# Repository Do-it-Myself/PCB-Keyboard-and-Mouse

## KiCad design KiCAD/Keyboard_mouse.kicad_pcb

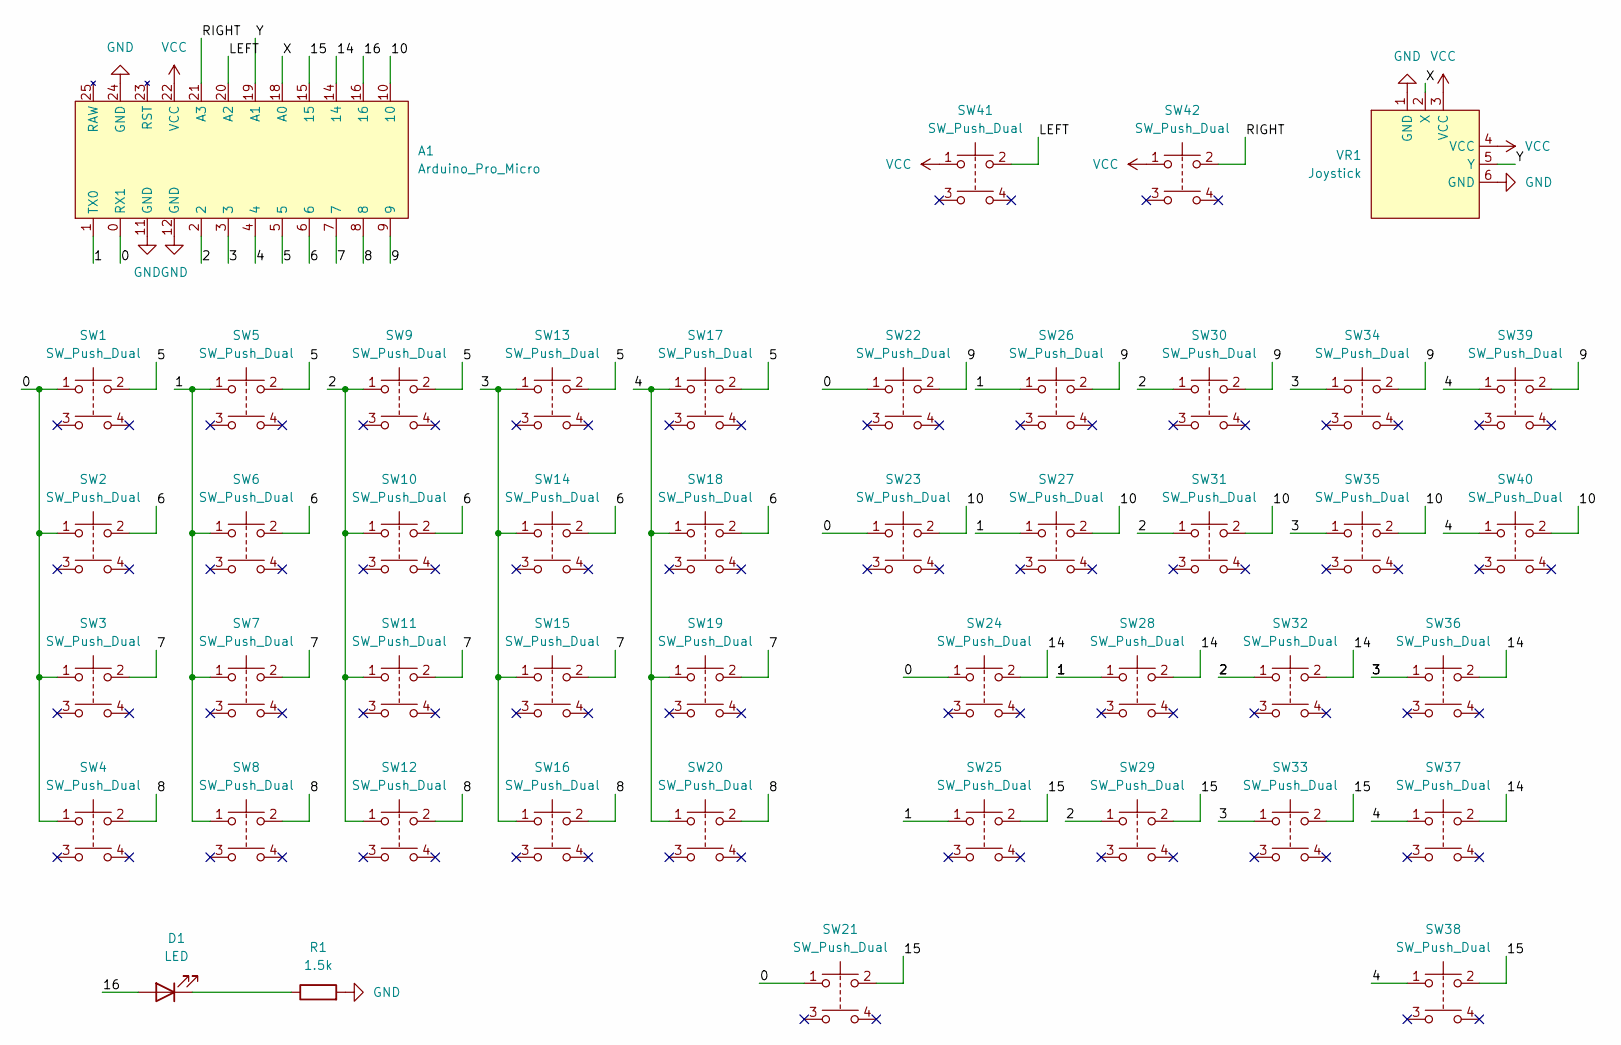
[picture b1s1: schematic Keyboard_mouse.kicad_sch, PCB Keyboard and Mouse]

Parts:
A1: Arduino_Pro_Micro
D1: LED; LED_D3.0mm
R1: 1.5k; R_Axial_DIN0204_L3.6mm_D1.6mm_P7.62mm_Horizontal
SW1, SW2, SW3, SW4, SW5, SW6, SW7, SW8, SW9, SW10, SW11, SW12, SW13, SW14, SW15, SW16, SW17, SW18, SW19, SW20, SW21, SW22, SW23, SW24, SW25, SW26, SW27, SW28, SW29, SW30, SW31, SW32, SW33, SW34, SW35, SW36, SW37, SW38, SW39, SW40, SW41, SW42: SW_Push_Dual; Push_Button
VR1: Joystick

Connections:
/0: A1.0 (RX1), SW1.1, SW2.1, SW3.1, SW4.1, SW21.1, SW22.1, SW23.1, SW24.1
/1: A1.1 (TX0), SW5.1, SW6.1, SW7.1, SW8.1, SW25.1, SW26.1, SW27.1, SW28.1
/2: A1.2, SW9.1, SW10.1, SW11.1, SW12.1, SW29.1, SW30.1, SW31.1, SW32.1
/3: A1.3, SW13.1, SW14.1, SW15.1, SW16.1, SW33.1, SW34.1, SW35.1, SW36.1
/4: A1.4, SW17.1, SW18.1, SW19.1, SW20.1, SW37.1, SW38.1, SW39.1, SW40.1
/5: A1.5, SW1.2, SW5.2, SW9.2, SW13.2, SW17.2
/6: A1.6, SW2.2, SW6.2, SW10.2, SW14.2, SW18.2
/7: A1.7, SW3.2, SW7.2, SW11.2, SW15.2, SW19.2
/8: A1.8, SW4.2, SW8.2, SW12.2, SW16.2, SW20.2
/9: A1.9, SW22.2, SW26.2, SW30.2, SW34.2, SW39.2
/10: A1.10, SW23.2, SW27.2, SW31.2, SW35.2, SW40.2
/14: A1.14, SW24.2, SW28.2, SW32.2, SW36.2, SW37.2
/15: A1.15, SW21.2, SW25.2, SW29.2, SW33.2, SW38.2
/16: A1.16, D1.2 (A)
/LEFT: A1.20 (A2), SW41.2
/RIGHT: A1.21 (A3), SW42.2
/X: A1.18 (A0), VR1.2 (X)
/Y: A1.19 (A1), VR1.5 (Y)
GND: A1.11 (GND), A1.12 (GND), A1.24 (GND), R1.2, VR1.1 (GND), VR1.6 (GND)
unnamed: D1.1 (K), R1.1
VCC: A1.22 (VCC), SW41.1, SW42.1, VR1.3 (VCC), VR1.4 (VCC)

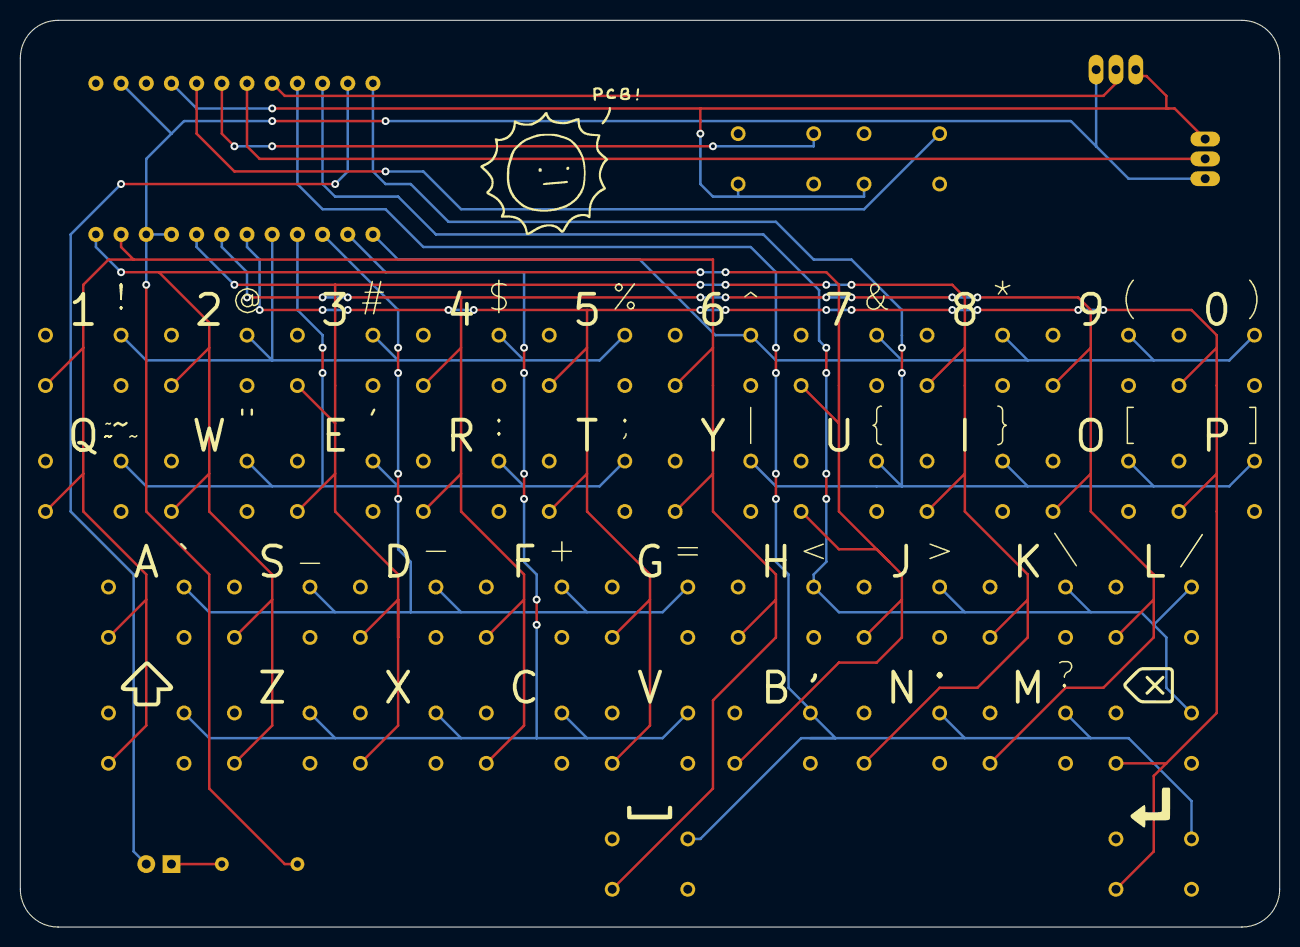
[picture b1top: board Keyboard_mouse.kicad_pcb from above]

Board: 2 copper layers, 127.0 x 91.4 mm, 46 parts (0 on the bottom side), 21 nets.
